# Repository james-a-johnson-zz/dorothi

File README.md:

# Dorothi Battlebot

The best bot to exist since sliced bread was invented.

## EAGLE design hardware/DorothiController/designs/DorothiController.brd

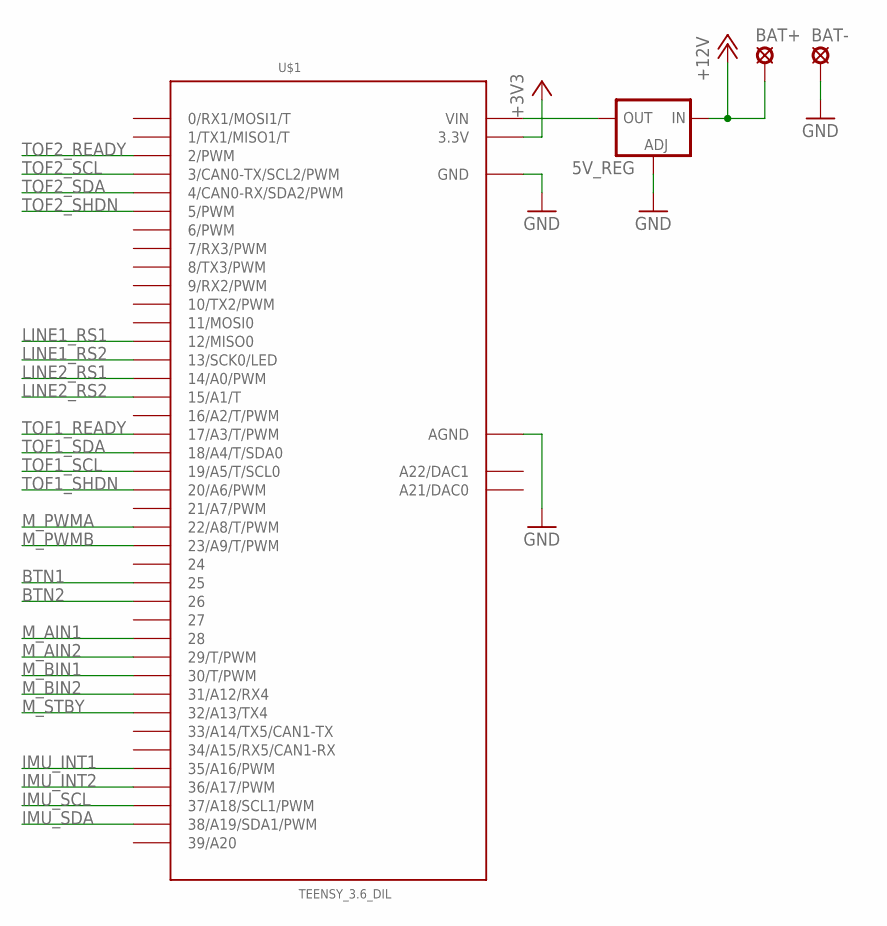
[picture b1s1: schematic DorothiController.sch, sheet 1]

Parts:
5V_REG: LM138-TL; TO220L1
BAT+: 24_SOLPAD; WIRE_SOLPAD
BAT-: 24_SOLPAD; WIRE_SOLPAD
U$1: TEENSY_3.6_DIL

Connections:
+3V3: U$1.3.3V, U$1.3.3V3 (3.3V); also elsewhere on the board
+12V: 5V_REG.3 (IN), BAT+.P$1; also elsewhere on the board
BTN1: U$1.25; also elsewhere on the board
BTN2: U$1.26; also elsewhere on the board
GND: 5V_REG.1 (ADJ), BAT-.P$1, U$1.AGND, U$1.GND, U$1.GND1 (GND); also elsewhere on the board
IMU_INT1: U$1.35/A16 (35/A16/PWM); also elsewhere on the board
IMU_INT2: U$1.36/A17 (36/A17/PWM); also elsewhere on the board
IMU_SCL: U$1.37/A18 (37/A18/SCL1/PWM); also elsewhere on the board
IMU_SDA: U$1.38/A19 (38/A19/SDA1/PWM); also elsewhere on the board
LINE1_RS1: U$1.12 (12/MISO0); also elsewhere on the board
LINE1_RS2: U$1.13 (13/SCK0/LED); also elsewhere on the board
LINE2_RS1: U$1.14/A0 (14/A0/PWM); also elsewhere on the board
LINE2_RS2: U$1.15/A1 (15/A1/T); also elsewhere on the board
M_AIN1: U$1.28; also elsewhere on the board
M_AIN2: U$1.29 (29/T/PWM); also elsewhere on the board
M_BIN1: U$1.30 (30/T/PWM); also elsewhere on the board
M_BIN2: U$1.31/A12 (31/A12/RX4); also elsewhere on the board
M_PWMA: U$1.22/A8 (22/A8/T/PWM); also elsewhere on the board
M_PWMB: U$1.23/A9 (23/A9/T/PWM); also elsewhere on the board
M_STBY: U$1.32/A13 (32/A13/TX4); also elsewhere on the board
unnamed: 5V_REG.2 (OUT), U$1.VIN
TOF1_READY: U$1.17/A3 (17/A3/T/PWM); also elsewhere on the board
TOF1_SCL: U$1.19/A5 (19/A5/T/SCL0); also elsewhere on the board
TOF1_SDA: U$1.18/A4 (18/A4/T/SDA0); also elsewhere on the board
TOF1_SHDN: U$1.20/A6 (20/A6/PWM); also elsewhere on the board
TOF2_READY: U$1.2 (2/PWM); also elsewhere on the board
TOF2_SCL: U$1.3 (3/CAN0-TX/SCL2/PWM); also elsewhere on the board
TOF2_SDA: U$1.4 (4/CAN0-RX/SDA2/PWM); also elsewhere on the board
TOF2_SHDN: U$1.5 (5/PWM); also elsewhere on the board

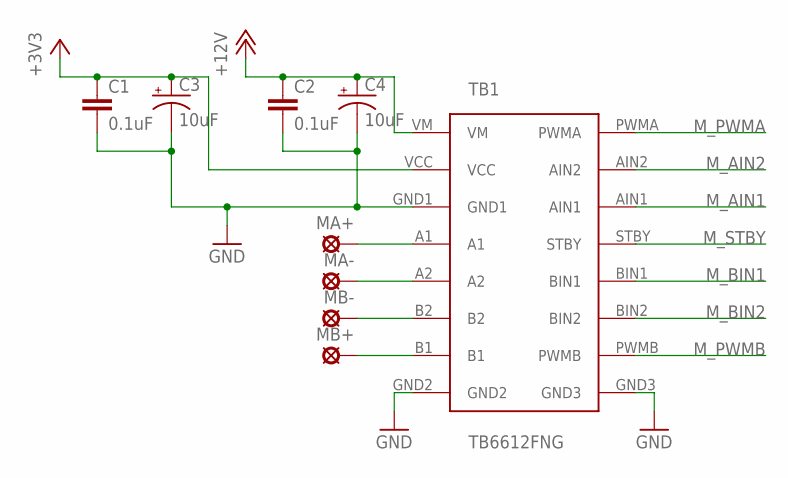
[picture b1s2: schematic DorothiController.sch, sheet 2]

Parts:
C1, C2: 0.1uF; 0603
C3, C4: 10uF; EIA3528
MA+: 24_SOLPAD; WIRE_SOLPAD
MA-: 24_SOLPAD; WIRE_SOLPAD
MB+: 24_SOLPAD; WIRE_SOLPAD
MB-: 24_SOLPAD; WIRE_SOLPAD
TB1: TB6612FNG

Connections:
+3V3: C1.1, C3.A (+), TB1.VCC; also elsewhere on the board
+12V: C2.1, C4.A (+), TB1.VM; also elsewhere on the board
GND: C1.2, C2.2, C3.C (-), C4.C (-), TB1.GND1, TB1.GND2, TB1.GND3; also elsewhere on the board
MA+: MA+.P$1, TB1.A1
MA-: MA-.P$1, TB1.A2
MB+: MB+.P$1, TB1.B1
MB-: MB-.P$1, TB1.B2
M_AIN1: TB1.AIN1; also elsewhere on the board
M_AIN2: TB1.AIN2; also elsewhere on the board
M_BIN1: TB1.BIN1; also elsewhere on the board
M_BIN2: TB1.BIN2; also elsewhere on the board
M_PWMA: TB1.PWMA; also elsewhere on the board
M_PWMB: TB1.PWMB; also elsewhere on the board
M_STBY: TB1.STBY; also elsewhere on the board

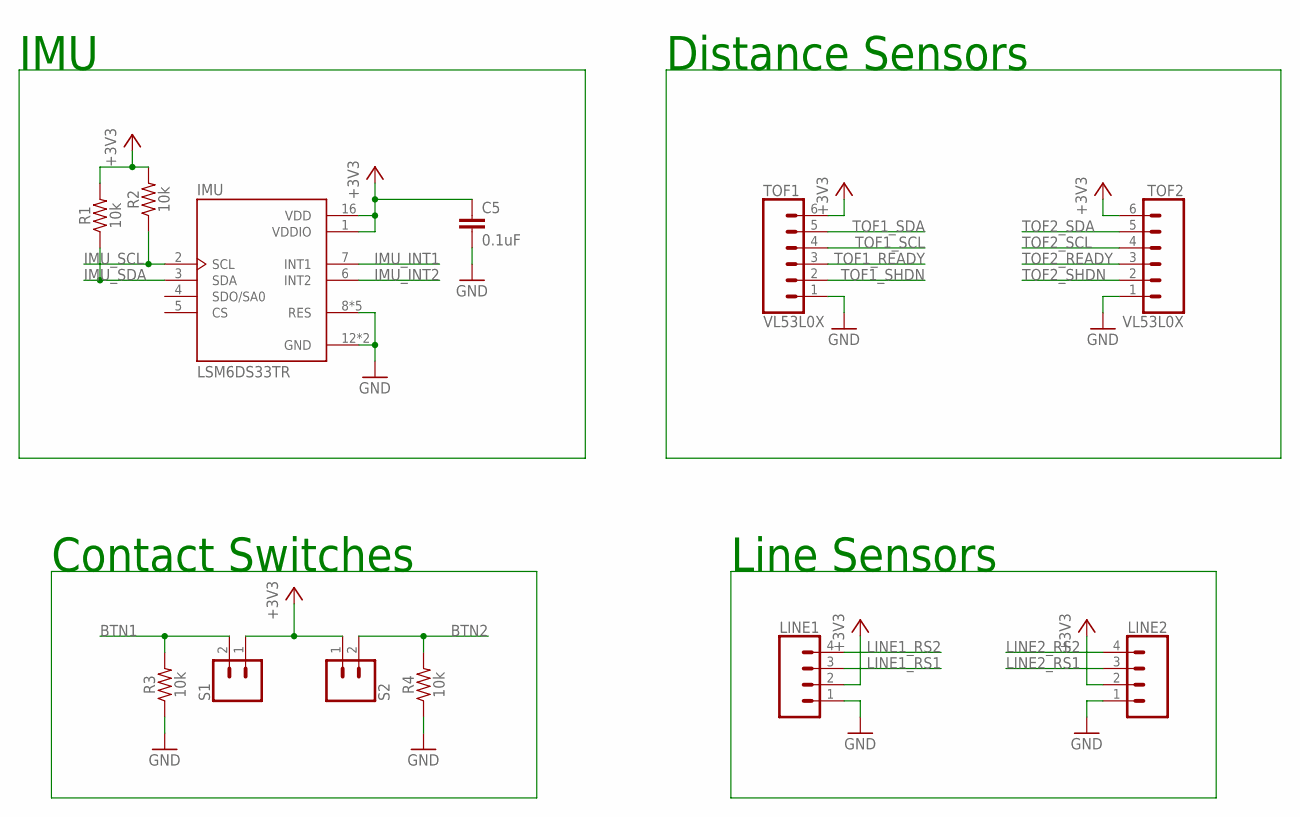
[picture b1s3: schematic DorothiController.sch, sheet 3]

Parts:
C5: 0.1uF; 0603
IMU: LSM6DS33TR; PQFN50P300X300X86-16N
LINE1, LINE2: CONN_04; 1X04
R1, R2, R3, R4: 10k; 0603
S1, S2: CONN_02; 1X02
TOF1, TOF2: VL53L0X; 1X06

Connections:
+3V3: C5.1, IMU.1 (VDDIO), IMU.16 (VDD), LINE1.2, LINE2.2, R1.2, R2.2, S1.1, S2.1, TOF1.6, TOF2.6; also elsewhere on the board
BTN1: R3.2, S1.2; also elsewhere on the board
BTN2: R4.2, S2.2; also elsewhere on the board
GND: C5.2, IMU.8 (RES), IMU.9 (RES), IMU.10 (RES), IMU.11 (RES), IMU.12 (GND), IMU.13 (GND), IMU.15 (RES), LINE1.1, LINE2.1, R3.1, R4.1, TOF1.1, TOF2.1; also elsewhere on the board
IMU_INT1: IMU.7 (INT1); also elsewhere on the board
IMU_INT2: IMU.6 (INT2); also elsewhere on the board
IMU_SCL: IMU.2 (SCL), R2.1; also elsewhere on the board
IMU_SDA: IMU.3 (SDA), R1.1; also elsewhere on the board
LINE1_RS1: LINE1.3; also elsewhere on the board
LINE1_RS2: LINE1.4; also elsewhere on the board
LINE2_RS1: LINE2.3; also elsewhere on the board
LINE2_RS2: LINE2.4; also elsewhere on the board
TOF1_READY: TOF1.3; also elsewhere on the board
TOF1_SCL: TOF1.4; also elsewhere on the board
TOF1_SDA: TOF1.5; also elsewhere on the board
TOF1_SHDN: TOF1.2; also elsewhere on the board
TOF2_READY: TOF2.3; also elsewhere on the board
TOF2_SCL: TOF2.4; also elsewhere on the board
TOF2_SDA: TOF2.5; also elsewhere on the board
TOF2_SHDN: TOF2.2; also elsewhere on the board

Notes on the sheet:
IMU
Distance Sensors
Line Sensors
Contact Switches

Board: 2 copper layers, 25 parts (0 on the bottom side), 33 nets, no tracks yet.

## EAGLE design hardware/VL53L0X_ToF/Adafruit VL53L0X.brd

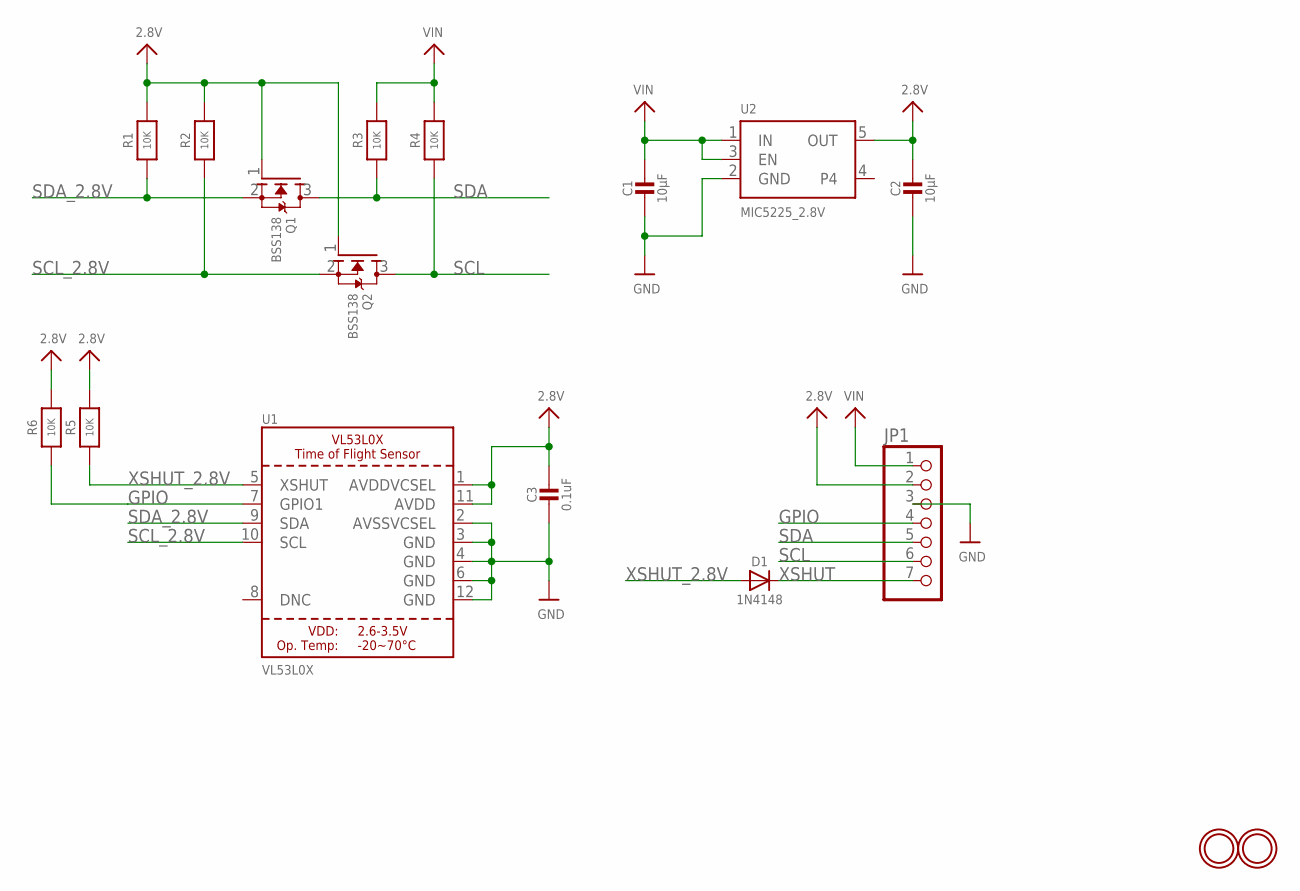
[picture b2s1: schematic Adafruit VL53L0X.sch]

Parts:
C1, C2: 10µF; 0805-NO
C3: 0.1uF; 0805-NO
D1: 1N4148; SOD-323
JP1: HEADER-1X770MIL; 1X07_ROUND_70
Q1, Q2: BSS138; SOT23-WIDE
R1, R2, R3, R4, R5, R6: 10K; 0805-NO
U1: VL53L0X; LGA12_ST
U2: MIC5225_2.8V; SOT23-5
U$13, U$14: MOUNTINGHOLE2.5; MOUNTINGHOLE_2.5_PLATED

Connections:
2.8V: C2.1, C3.1, JP1.2, Q1.1 (G), Q2.1 (G), R1.2, R2.2, R5.2, R6.2, U1.1 (AVDDVCSEL), U1.11 (AVDD), U2.5 (OUT)
GND: C1.2, C2.2, C3.2, JP1.3, U1.2 (AVSSVCSEL), U1.3 (GND), U1.4 (GND), U1.6 (GND), U1.12 (GND), U2.2 (GND)
GPIO: JP1.4, R6.1, U1.7 (GPIO1)
SCL: JP1.6, Q2.3 (D), R4.1
SCL_2.8V: Q2.2 (S), R2.1, U1.10 (SCL)
SDA: JP1.5, Q1.3 (D), R3.1
SDA_2.8V: Q1.2 (S), R1.1, U1.9 (SDA)
VIN: C1.1, JP1.1, R3.2, R4.2, U2.1 (IN), U2.3 (EN)
XSHUT: D1.C, JP1.7
XSHUT_2.8V: D1.A, R5.1, U1.5 (XSHUT)

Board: 2 copper layers, 17 parts (0 on the bottom side), 10 nets, no tracks yet.

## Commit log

2018-10-26 Added readme
2018-10-26 Created a particle project
2018-10-27 cleaned up directory structure
2018-10-27 Initial makefile
2018-10-27 Make file can now write to photon
2018-11-16 Did a change
2018-11-16 adafruit hardware
2018-11-17 Trading off PCB design to Binit
2018-11-24 schematic of controller completed
2018-11-24 general idea of board layout added
2018-11-29 controller ready
2018-11-30 revert to original design by adafruit
2018-11-30 silkscreen and status diode

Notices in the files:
parts and their libraries:
SparkFun-Capacitors: Licensing: Creative Commons ShareAlike 4.0 International - https://creativecommons.org/licenses/by-sa/4.0
microbuilder: This work is placed in the public domain, and may be freely used for commercial and non-commercial work with the following conditions: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
